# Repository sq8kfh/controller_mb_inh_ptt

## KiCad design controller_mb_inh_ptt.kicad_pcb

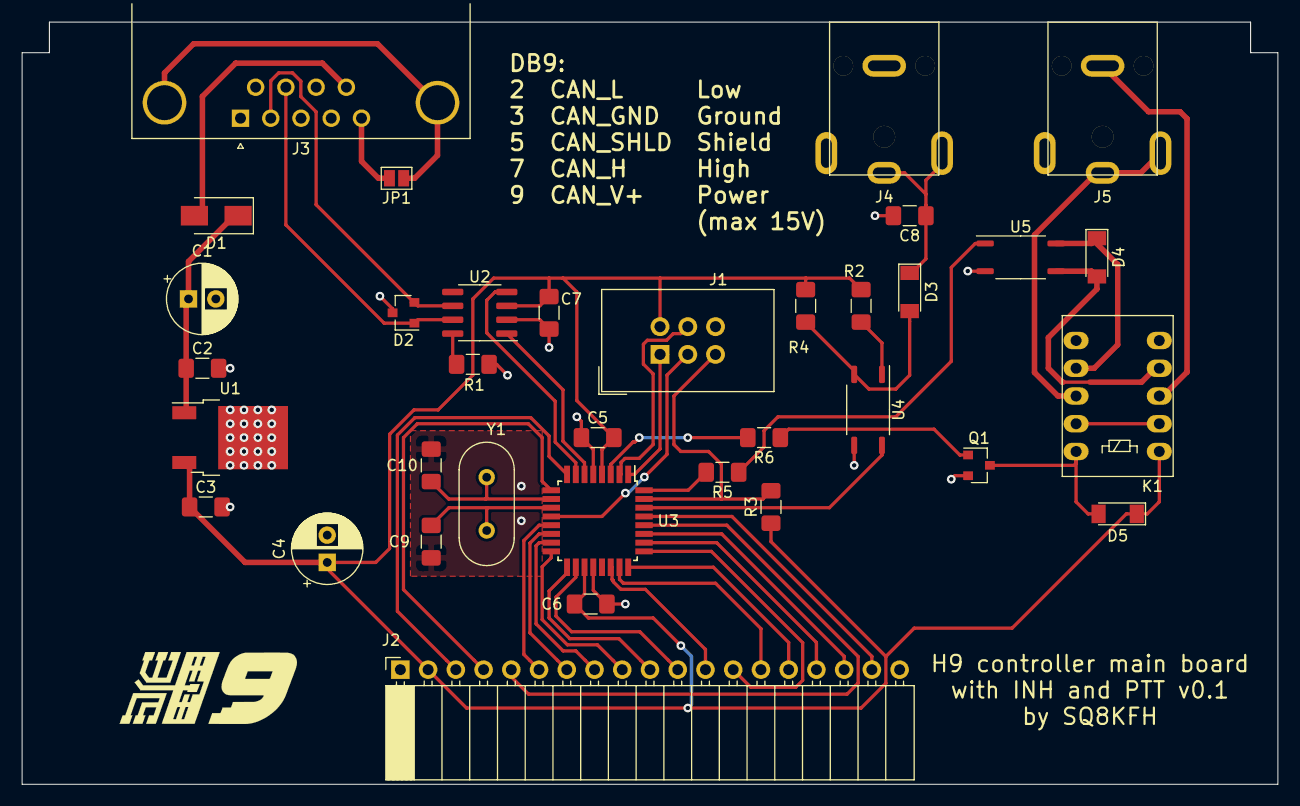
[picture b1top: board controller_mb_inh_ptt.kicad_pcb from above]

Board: 2 copper layers, 115.0 x 69.8 mm, 35 parts (0 on the bottom side), 47 nets.

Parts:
C1: 100uF; CP_Radial_D6.3mm_P2.50mm
C2, C3, C5, C6, C7, C8: 100nF; C_1206_3216Metric_Pad1.42x1.75mm_HandSolder
C4: 47uF; CP_Radial_D6.3mm_P2.50mm
C9, C10: 22pF; C_1206_3216Metric_Pad1.42x1.75mm_HandSolder
D1: S1A; D_SMA
D2: NUP2105L; SOT-23
D3, D4, D5: 4148; D_MiniMELF
J1: AVR-ISP-6; IDC-Header_2x03_P2.54mm_Vertical
J2: Front panel; PinSocket_1x19_P2.54mm_Horizontal
J3: CAN; DSUB-9_Female_Horizontal_P2.77x2.84mm_EdgePinOffset7.70mm_H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
J4: PTT; LUMBERG_1553
J5: INH; LUMBERG_1553
JP1: Shield; SolderJumper-2_P1.3mm_Open_Pad1.0x1.5mm
K1: AZ850/RSM850; Relay_DPDT_FRT5
Q1: BC817; SOT-23
R1: 39k; R_1206_3216Metric_Pad1.42x1.75mm_HandSolder
R2, R5: 390R; R_1206_3216Metric_Pad1.42x1.75mm_HandSolder
R3, R4: 10k; R_1206_3216Metric_Pad1.42x1.75mm_HandSolder
R6: 1k5; R_1206_3216Metric_Pad1.42x1.75mm_HandSolder
U1: LM78M05; TO-252-2
U2: MCP2551-I-SN; SOIC-8_3.9x4.9mm_P1.27mm
U3: ATmega32M1-AU; TQFP-32_7x7mm_P0.8mm
U4, U5: TLP185; SOIC-4_4.55x3.7mm_P2.54mm
Y1: 12MHz; Crystal_HC49-U_Vertical

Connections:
+5V: C3.1, C4.1, C5.2, C6.1, C7.2, D5.1, J1.2, J2.2, K1.1, R2.2, R3.1, R4.1, U1.3, U2.3, U3.4, U3.19
/CAN_H: D2.1, J3.7, U2.7
/CAN_L: D2.2, J3.2, U2.6
/CAN_RX: U2.4, U3.7
/CAN_TX: U2.1, U3.6
/INH: R5.2, U3.32
/INH_BP: R6.2, U3.3
/MISO: J1.1, U3.1
/MOSI: J1.4, U3.2
/PB0(MISO): J2.3, U3.8
/PB1(MOSI): J2.4, U3.9
/PB2(INT1): J2.9, U3.16
/PB3: J2.14, U3.23
/PB4: J2.15, U3.24
/PB5(INT2): J2.16, U3.26
/PB6: J2.17, U3.27
/PB7(SCK): J2.5, U3.28
/PC4: J2.10, U3.17
/PC5: J2.11, U3.18
/PC6: J2.12, U3.22
/PC7(D2A): J2.13, U3.25
/PD0: J2.18, U3.29
/PD5: J2.6, U3.13
/PD6: J2.7, U3.14
/PD7: J2.8, U3.15
/PTT_IN: U3.30, U4.6
/RST: J1.5, R3.2, U3.31
/SCK: J1.3, U3.12
GND: C1.2, C2.2, C3.2, C4.2, C5.1, C6.2, C7.1, C8.2, C9.2, C10.2, D2.3, J1.6, J2.1, J3.3, J4.2, Q1.2, R1.2, U1.2, U2.2, U3.5, U3.20, U4.4, U5.3
unnamed: C1.1, C2.1, D1.1, U1.1
unnamed: C8.1, D3.1, J4.1
unnamed: C9.1, U3.11, Y1.1
unnamed: C10.1, U3.10, Y1.2
unnamed: D1.2, J3.9
unnamed: D3.2, R4.2, U4.3
unnamed: D4.1, K1.7, U5.6
unnamed: D4.2, K1.4, U5.4
unnamed: D5.2, K1.10, Q1.3
unnamed: J3.0, JP1.1
unnamed: J3.5, JP1.2
unnamed: J5.1, K1.8
unnamed: J5.2, K1.3
unnamed: K1.2, K1.9
unnamed: Q1.1, R6.1
unnamed: R1.1, U2.8
unnamed: R2.1, U4.1
unnamed: R5.1, U5.1

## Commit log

2020-12-24 Init
2020-12-24 v0.1
